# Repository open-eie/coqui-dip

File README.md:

coqui-dip
=========

through-hole (DIP) design for the coqui, using a dual 555 timer chip

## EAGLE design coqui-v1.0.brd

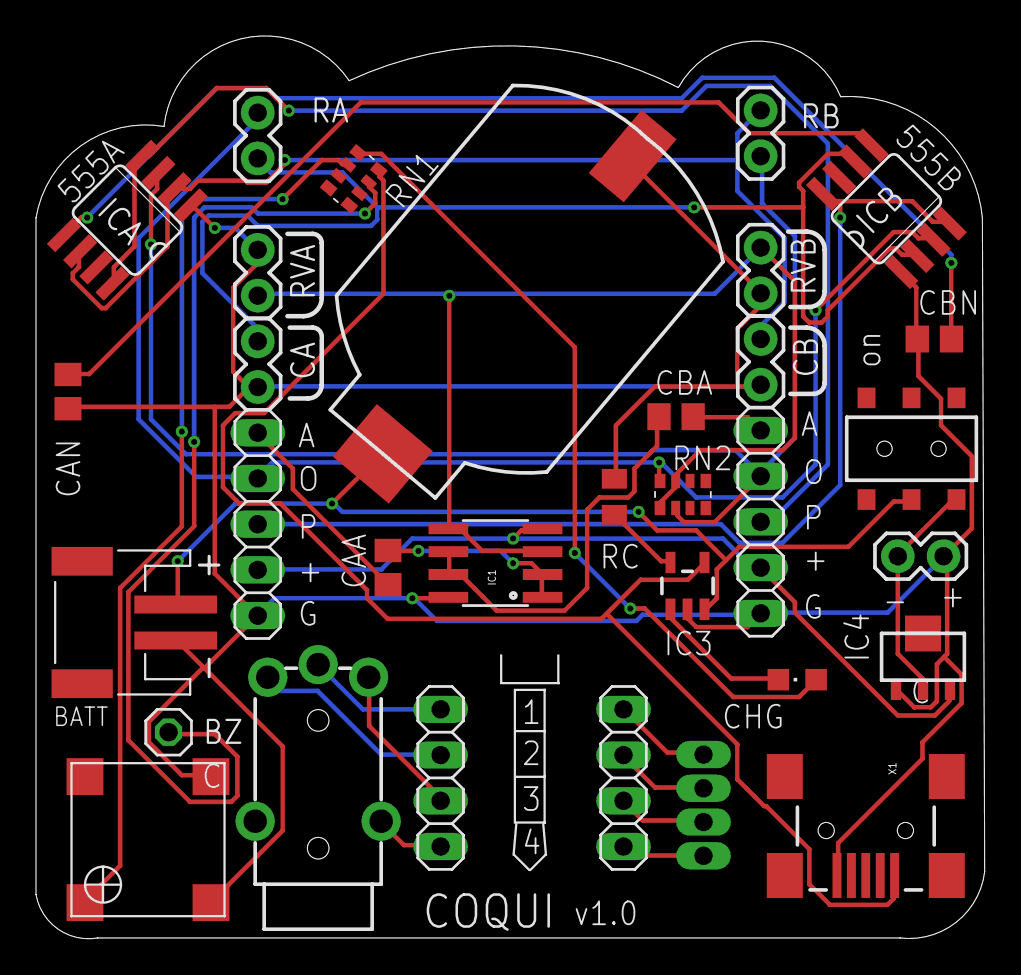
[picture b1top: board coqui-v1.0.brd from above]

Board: 2 copper layers, 52.7 x 50.2 mm, 32 parts (0 on the bottom side), 31 nets.

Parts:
BAT1: LIR2032; BATTCOM_20MM_PTH_SMT
BATT: JST-PH-2-SMT-RA
BZ: 1X01
CA: M02PTH; 1X02
CAA: 0.01uF; C0805@1
CAN: 0.01uF; C0805@1
CB: M02PTH; 1X02
CBA: 0.01uF; C0805@1
CBN: 0.01uF; C0805@1
CHG: 0805; CHIPLED_0805
IC1: OPAMP-DUALU; SO08
IC3: MCP73831; SOT23-5
IC4: MCP1700-33; SOT89
ICA: LM555D; SO08
ICB: LM555D; SO08
J1: AYZ0202
J-FEMALE: MJ-2135
JP1: 1X04/90
JP2, JP5: 1X05
JP3, JP4: 1X04
PWR: M02PTH; 1X02
RA: M02PTH; 1X02
RB: M02PTH; 1X02
RC: 22K; R0805
RN1, RN2: EXB38V
RVA: M02PTH; 1X02
RVB: M02PTH; 1X02
U$1: BUZZER; SMT-8585-BUZZER
X1: USBSMD; USB-MINIB

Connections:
AOUT: ICB.3, JP2.4, RA.2, RN2.8
BOUT: ICA.3, JP5.4, RB.2, RN2.2
GND: BAT1.P$1, BATT.2, CA.1, CAN.1, CB.1, CBN.1, IC1.8, IC3.2, IC4.1, ICA.1, ICB.1, JP2.1, JP5.1, PWR.2, RC.1, RVA.2, RVB.1, U$1.-, U$1.A-, X1.GND
unnamed: J-FEMALE.1, JP4.1
unnamed: J-FEMALE.2, JP4.2
unnamed: IC3.5, RC.2
unnamed: J-FEMALE.3, JP4.3
unnamed: CHG.C, IC3.1
unnamed: J-FEMALE.4, JP4.4
unnamed: BZ.1, RN1.7
unnamed: CHG.A, RN1.1
unnamed: CAA.1, JP2.5
unnamed: CAA.2, IC1.1, IC1.2
unnamed: CA.2, ICB.2, ICB.6, RA.1
unnamed: RN1.2, U$1.+
unnamed: CBA.2, JP5.5
unnamed: CAN.2, ICB.5
unnamed: CBN.2, ICA.5
unnamed: CB.2, ICA.2, ICA.6, RB.1
unnamed: JP1.1, JP3.4
unnamed: JP1.3, JP3.1
unnamed: JP1.2, JP3.3
unnamed: JP1.4, JP3.2
unnamed: IC1.3, IC1.5, RN2.1, RN2.7, RVA.1, RVB.2
unnamed: CBA.1, IC1.6, IC1.7
VAIN: ICB.4, ICB.8, JP2.3
VBAT: BAT1.P$2, BATT.1, IC3.3, J1.2
VBIN: ICA.4, ICA.8, JP5.3
VBUS: IC3.4, RN1.8, X1.VBUS
VCC: IC1.4, IC4.3, JP2.2, JP5.2
VDD: IC4.2, J1.1, PWR.1

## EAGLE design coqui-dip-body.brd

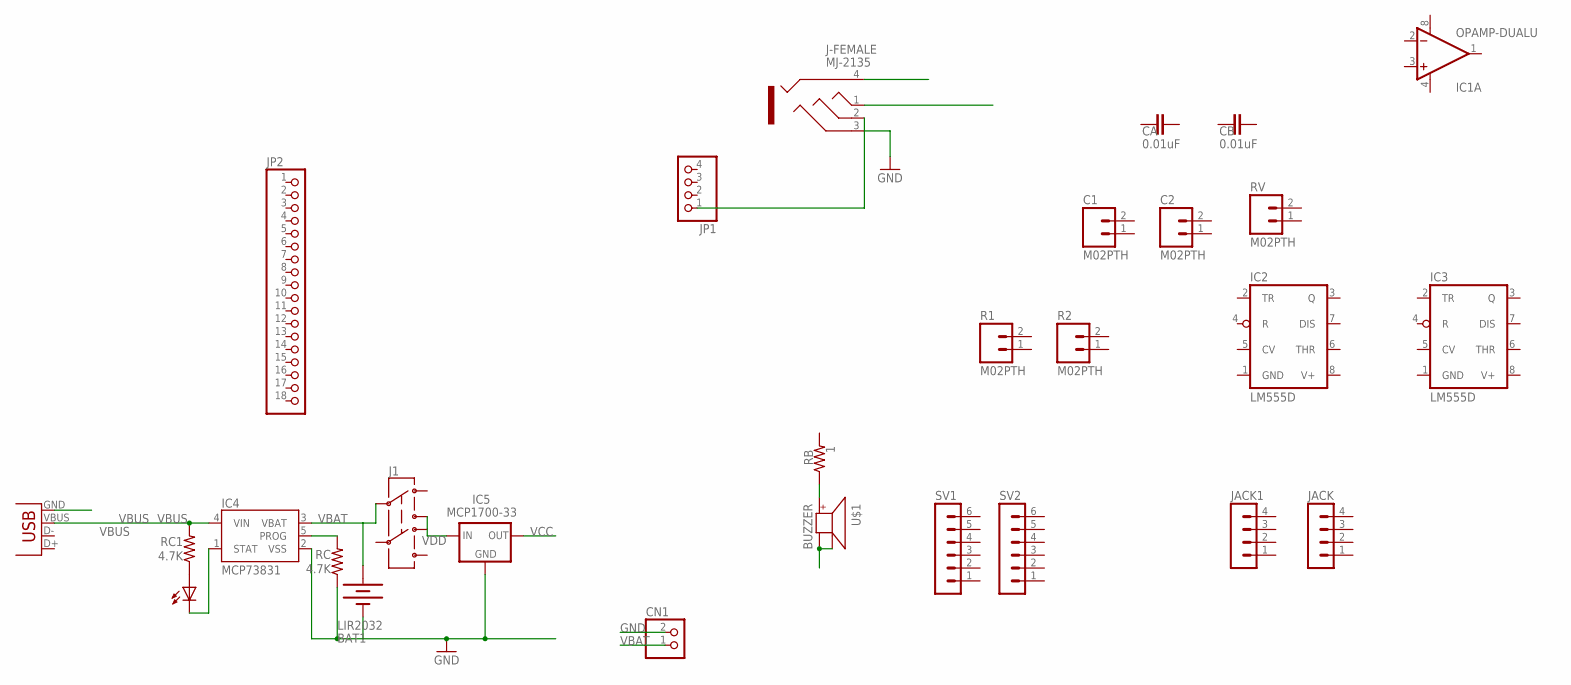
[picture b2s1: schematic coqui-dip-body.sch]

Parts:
BAT1: LIR2032; BATTCOM_20MM_PTH_SMT
C1, C2: M02PTH; 1X02
CA: 0.01uF; C0805@1
CB: 0.01uF; C0805@1
CHG: 0805; CHIPLED_0805
CN1: JST_2PIN-SMT-RA; JST-PH-2-SMT-RA
IC1: OPAMP-DUALU; SO08
IC2, IC3: LM555D; SO08
IC4: MCP73831; SOT23-5
IC5: MCP1700-33; SOT89
J1: AYZ0202
J-FEMALE: MJ-2135
JACK, JACK1: MA04-1
JP1: PINHD-1X4/90; 1X04/90
JP2: PINHD-1X18; 1X18
R1, R2: M02PTH; 1X02
RB: 1; R0805
RC, RC1: 4.7K; R0805
RV: M02PTH; 1X02
SV1, SV2: MA06-1
U$1: BUZZER; SMT-8585-BUZZER
X1: USBSMD; USB-MINIB

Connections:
GND: BAT1.P$1 (-), CN1.2 (1), IC2.1 (GND), IC3.1 (GND), IC4.2 (VSS), IC5.1 (GND), J-FEMALE.3, RC.1
unnamed: J-FEMALE.2, JP1.1
unnamed: IC4.5 (PROG), RC.2
unnamed: CHG.C, IC4.1 (STAT)
unnamed: U$1.-, U$1.A-
unnamed: CHG.A, RC1.1
unnamed: RB.1, U$1.+
V+: IC1.8 (V+), IC2.8 (V+), IC3.8 (V+)
V-: IC1.4 (V-)
VBAT: BAT1.P$2 (+), CN1.1 (2), IC4.3 (VBAT), J1.2
VBUS: IC4.4 (VIN), RC1.2, X1.VBUS
VCC: IC5.3 (OUT)
VDD: IC5.2 (IN), J1.1 (3)

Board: 2 copper layers, 28 parts (0 on the bottom side), 11 nets, no tracks yet.

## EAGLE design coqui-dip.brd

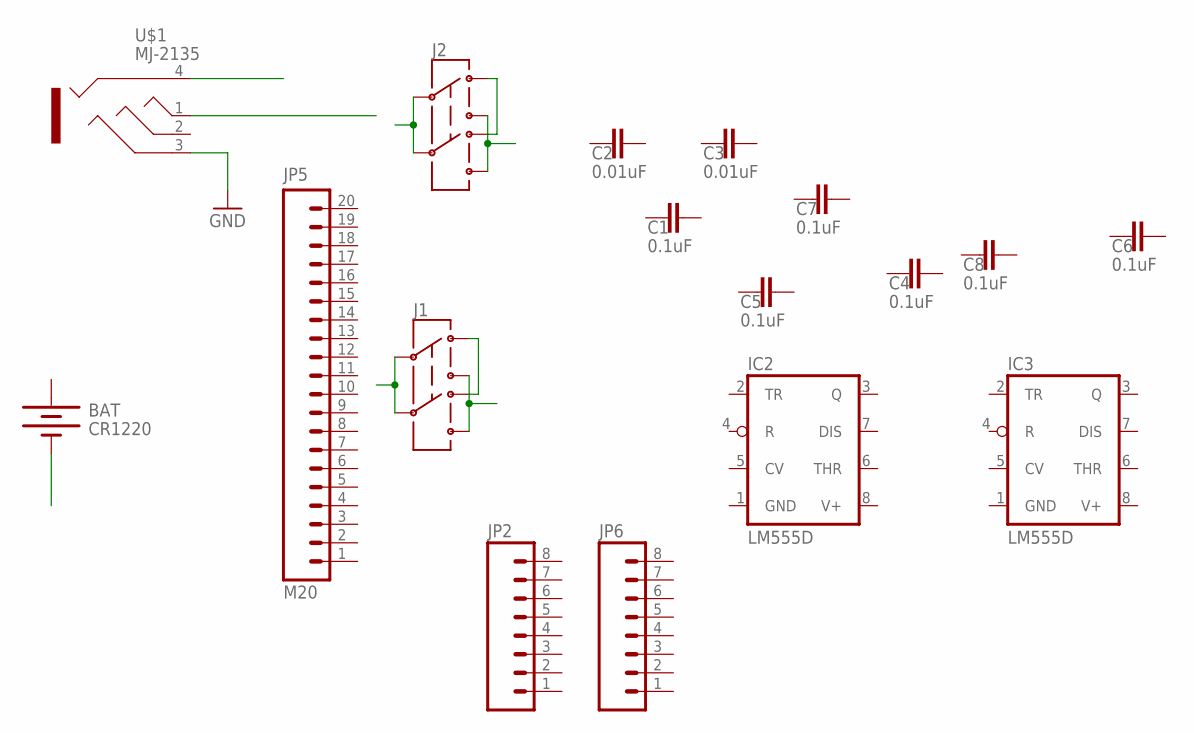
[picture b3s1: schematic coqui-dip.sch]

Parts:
BAT: CR1220; BATTCON_12MM_SMT
C1, C4, C5, C6, C7, C8: 0.1uF; C0805@1
C2, C3: 0.01uF; C0805@1
IC2, IC3: LM555D; SO08
J1, J2: AYZ0202
JP2, JP6: M081X08; 1X08
JP5: M20; 1X20
U$1: MJ-2135

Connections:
+: BAT.P$2 (+)
GND: IC2.1 (GND), IC3.1 (GND), U$1.3
GND1: BAT.P$1 (-)
unnamed: J1.3 (1), J1.6 (4)
unnamed: J2.3 (1), J2.6 (4)
V+: IC2.8 (V+), IC3.8 (V+)
VBAT: J1.2, J1.5
VBAT1: J2.2, J2.5
VDD: J1.1 (3), J1.4 (6)
VDD1: J2.1 (3), J2.4 (6)

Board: 2 copper layers, 17 parts (0 on the bottom side), 8 nets, no tracks yet.

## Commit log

2014-10-07 yes.

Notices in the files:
parts and their libraries:
SparkFun-Connectors: Licensing: Creative Commons ShareAlike 4.0 International - https://creativecommons.org/licenses/by-sa/4.0
